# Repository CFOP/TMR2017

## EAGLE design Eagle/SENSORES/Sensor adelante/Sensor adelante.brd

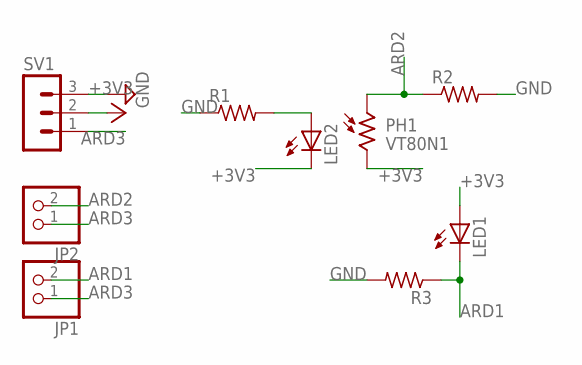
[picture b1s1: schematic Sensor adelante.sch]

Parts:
JP1, JP2: PINHD-1X2; 1X02
LED1, LED2: LED5MM
PH1: VT80N1; VT800
R1, R2, R3: R-US_0207/15; 0207/15
SV1: MA03-1

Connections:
+3V3: LED1.A, LED2.K (C), PH1.2, SV1.2
ARD1: JP1.2, LED1.K (C), R3.1
ARD2: JP2.2, PH1.1, R2.1
ARD3: JP1.1, JP2.1, SV1.1
GND: R1.1, R2.2, R3.2, SV1.3
unnamed: LED2.A, R1.2

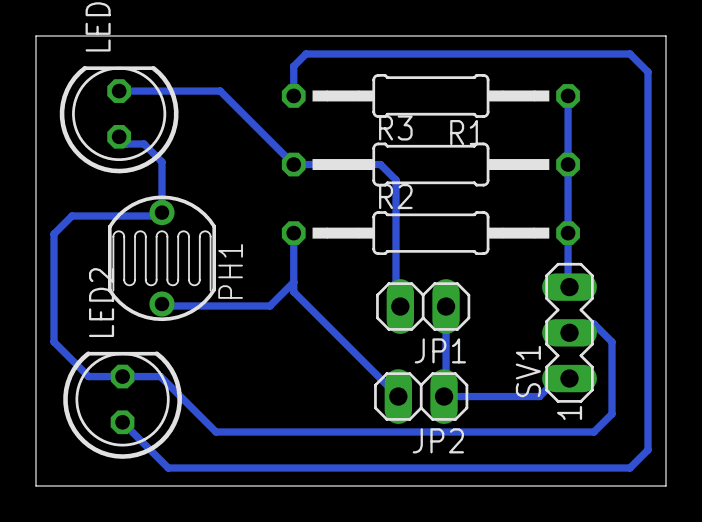
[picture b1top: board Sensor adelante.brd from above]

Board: 2 copper layers, 35.0 x 25.0 mm, 9 parts (0 on the bottom side), 6 nets.

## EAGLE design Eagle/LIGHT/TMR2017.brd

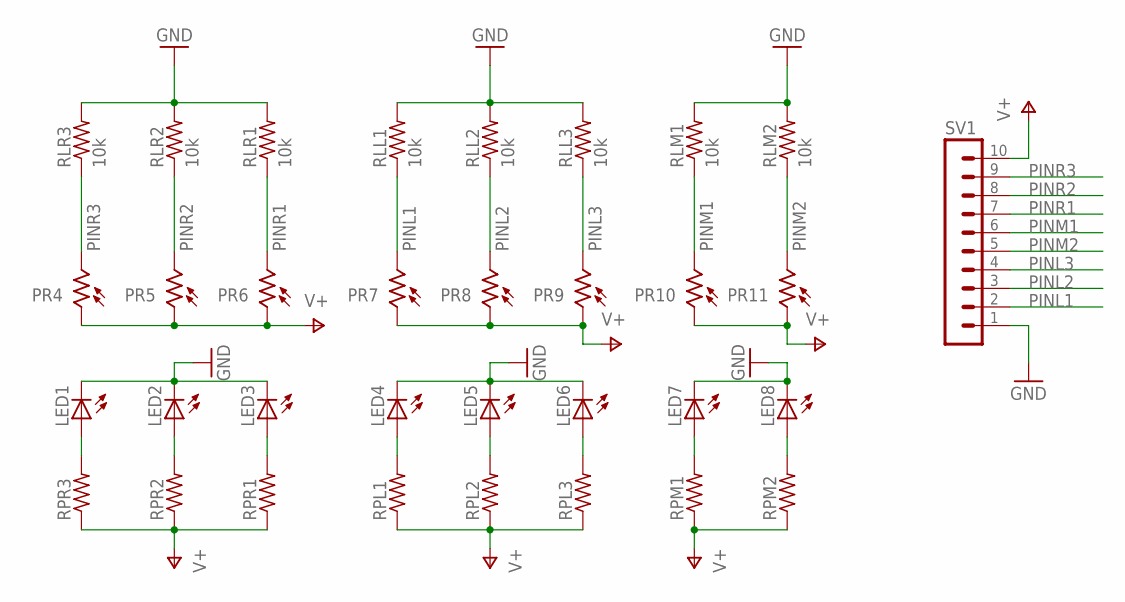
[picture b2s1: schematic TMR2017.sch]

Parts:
LED1, LED2, LED3, LED4, LED5, LED6, LED7, LED8: TLLR4400; LED3MM
PR4, PR5, PR6, PR7, PR8, PR9, PR10, PR11: VT80N1; VT800
RLL1, RLL2, RLL3: 10k; 0207/10
RLM1, RLM2: 10k; 0207/10
RLR1, RLR2, RLR3: 10k; 0207/10
RPL1, RPL2, RPL3: R-US_0207/10; 0207/10
RPM1, RPM2: R-US_0207/10; 0207/10
RPR1, RPR2, RPR3: R-US_0207/10; 0207/10
SV1: MA10-1

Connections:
GND: LED1.K (C), LED2.K (C), LED3.K (C), LED4.K (C), LED5.K (C), LED6.K (C), LED7.K (C), LED8.K (C), RLL1.2, RLL2.2, RLL3.2, RLM1.2, RLM2.2, RLR1.2, RLR2.2, RLR3.2, SV1.1
unnamed: LED1.A, RPR3.2
unnamed: LED2.A, RPR2.2
unnamed: LED3.A, RPR1.2
unnamed: LED4.A, RPL1.2
unnamed: LED5.A, RPL2.2
unnamed: LED6.A, RPL3.2
unnamed: LED7.A, RPM1.2
unnamed: LED8.A, RPM2.2
PINL1: PR7.2, RLL1.1, SV1.2
PINL2: PR8.2, RLL2.1, SV1.3
PINL3: PR9.2, RLL3.1, SV1.4
PINM1: PR10.2, RLM1.1, SV1.6
PINM2: PR11.2, RLM2.1, SV1.5
PINR1: PR6.2, RLR1.1, SV1.7
PINR2: PR5.2, RLR2.1, SV1.8
PINR3: PR4.2, RLR3.1, SV1.9
V+: PR4.1, PR5.1, PR6.1, PR7.1, PR8.1, PR9.1, PR10.1, PR11.1, RPL1.1, RPL2.1, RPL3.1, RPM1.1, RPM2.1, RPR1.1, RPR2.1, RPR3.1, SV1.10

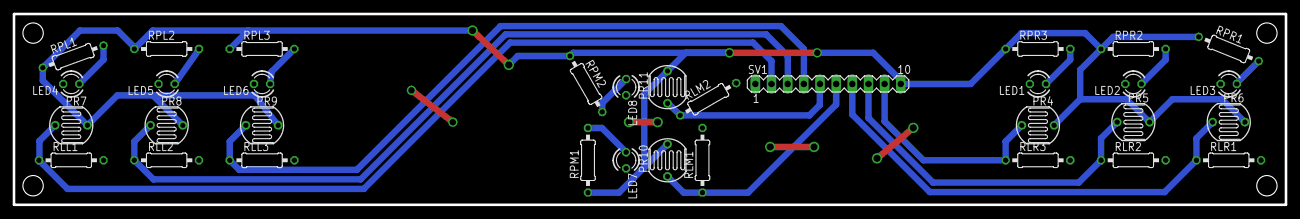
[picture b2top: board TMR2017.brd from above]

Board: 2 copper layers, 200.0 x 30.0 mm, 33 parts (0 on the bottom side), 18 nets.

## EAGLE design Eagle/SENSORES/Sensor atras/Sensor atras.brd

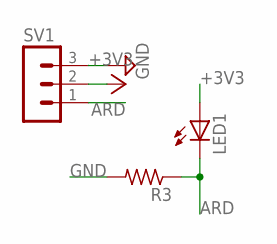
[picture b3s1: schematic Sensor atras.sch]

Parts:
LED1: LED5MM
R3: R-US_0207/15; 0207/15
SV1: MA03-1

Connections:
+3V3: LED1.A, SV1.2
ARD: LED1.K (C), R3.1, SV1.1
GND: R3.2, SV1.3

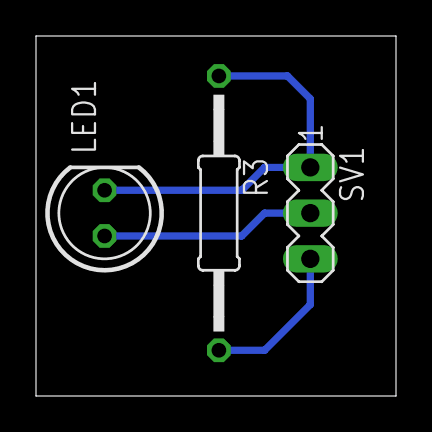
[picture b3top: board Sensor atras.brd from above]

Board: 2 copper layers, 20.0 x 20.0 mm, 3 parts (0 on the bottom side), 3 nets.

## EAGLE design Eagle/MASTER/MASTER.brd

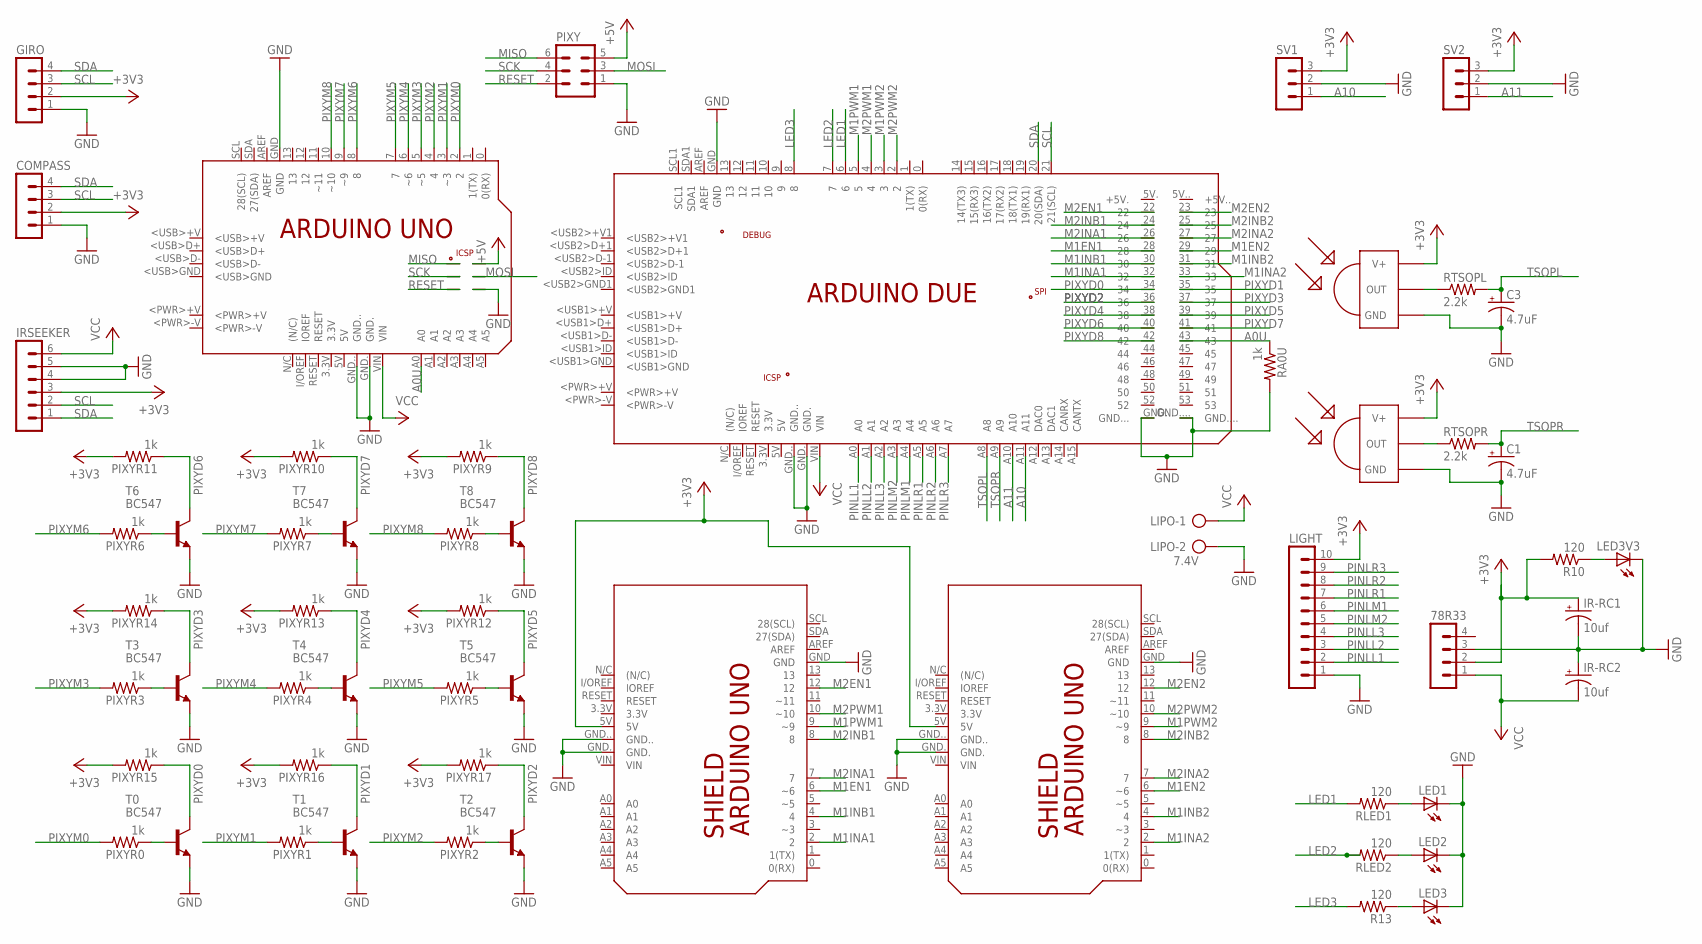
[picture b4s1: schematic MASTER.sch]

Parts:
78R33: MA04-1
C1, C3: 4.7uF; E5-6
COMPASS: MA04-1
GIRO: MA04-1
IR-RC1, IR-RC2: 10uf; E5-6
IRSEEKER: MA06-1
LED1, LED2, LED3, LED3V3: LED5MM
LIGHT: MA10-1
LIPO: 7.4V; AK500/2
PCB3: ARDUINO_DUE
PCB4: ARDUINO_UNO
PIXY: MA03-2
PIXYR0, PIXYR1, PIXYR2, PIXYR3, PIXYR4, PIXYR5, PIXYR6, PIXYR7, PIXYR8, PIXYR9, PIXYR10, PIXYR11, PIXYR12, PIXYR13, PIXYR14, PIXYR15, PIXYR16, PIXYR17: 1k; 0411/15
PUENTE, PUENTE2: SHIELD_UNO
R10, R13: 120; 0411/15
RA0U: 1k; 0411/15
RLED1, RLED2: 120; 0411/15
RTSOPL: 2.2k; 0411/15
RTSOPR: 2.2k; 0411/15
SV1, SV2: MA03-1
T0, T1, T2, T3, T4, T5, T6, T7, T8: BC547; TO92
TSOPL: TSOP2240; TSOP22XX
TSOPR: TSOP2240; TSOP22XX

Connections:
+3V3: 78R33.2, COMPASS.2, GIRO.2, IR-RC1.+, IRSEEKER.3, LIGHT.10, PIXYR9.2, PIXYR10.2, PIXYR11.2, PIXYR12.2, PIXYR13.2, PIXYR14.2, PIXYR15.2, PIXYR16.2, PIXYR17.2, PUENTE.5V, PUENTE2.5V, R10.2, SV1.3, SV2.3, TSOPL.VCC (V+), TSOPR.VCC (V+)
+5V: PCB4.+5V, PIXY.5
A0U: PCB3.43, PCB4.A0, RA0U.1
A10: PCB3.A11, SV1.1
A11: PCB3.A10, SV2.1
GND: 78R33.3, C1.-, C3.-, COMPASS.1, GIRO.1, IR-RC1.-, IR-RC2.+, IRSEEKER.4, IRSEEKER.5, LED1.K (C), LED2.K (C), LED3.K (C), LED3V3.K (C), LIGHT.1, LIPO.2, PCB3.GND, PCB3.GND., PCB3.GND.., PCB3.GND..., PCB3.GND...., PCB4.GND, PCB4.GND., PCB4.GND.., PCB4.GND_, PIXY.1, PUENTE.GND, PUENTE.GND., PUENTE.GND.., PUENTE2.GND, PUENTE2.GND., PUENTE2.GND.., RA0U.2, SV1.2, SV2.2, T0.1 (E), T1.1 (E), T2.1 (E), T3.1 (E), T4.1 (E), T5.1 (E), T6.1 (E), T7.1 (E), T8.1 (E), TSOPL.GND, TSOPR.GND
LED1: PCB3.6, RLED1.2
LED2: PCB3.7, RLED2.2
LED3: PCB3.8, R13.2
M1EN1: PCB3.28, PUENTE.6 (~6)
M1EN2: PCB3.29, PUENTE2.6 (~6)
M1INA1: PCB3.32, PUENTE.2
M1INA2: PCB3.33, PUENTE2.2
M1INB1: PCB3.30, PUENTE.4
M1INB2: PCB3.31, PUENTE2.4
M1PWM1: PCB3.5, PUENTE.9 (~9)
M1PWM2: PCB3.3, PUENTE2.9 (~9)
M2EN1: PCB3.22, PUENTE.12
M2EN2: PCB3.23, PUENTE2.12
M2INA1: PCB3.26, PUENTE.7
M2INA2: PCB3.27, PUENTE2.7
M2INB1: PCB3.24, PUENTE.8
M2INB2: PCB3.25, PUENTE2.8
M2PWM1: PCB3.4, PUENTE.10 (~10)
M2PWM2: PCB3.2, PUENTE2.10 (~10)
MISO: PCB4.MISO, PIXY.6
MOSI: PCB4.MOSI, PIXY.3
unnamed: RTSOPR.1, TSOPR.OUT
unnamed: LED1.A, RLED1.1
unnamed: RTSOPL.1, TSOPL.OUT
unnamed: PIXYR0.1, T0.2 (B)
unnamed: PIXYR1.1, T1.2 (B)
unnamed: PIXYR2.1, T2.2 (B)
unnamed: PIXYR3.1, T3.2 (B)
unnamed: PIXYR4.1, T4.2 (B)
unnamed: PIXYR5.1, T5.2 (B)
unnamed: PIXYR6.1, T6.2 (B)
unnamed: PIXYR7.1, T7.2 (B)
unnamed: PIXYR8.1, T8.2 (B)
unnamed: LED3V3.A, R10.1
PINLL1: LIGHT.2, PCB3.A0
PINLL2: LIGHT.3, PCB3.A1
PINLL3: LIGHT.4, PCB3.A2
PINLM1: LIGHT.6, PCB3.A4
PINLM2: LIGHT.5, PCB3.A3
PINLR1: LIGHT.7, PCB3.A5
PINLR2: LIGHT.8, PCB3.A6
PINLR3: LIGHT.9, PCB3.A7
PIXYD0: PCB3.34, PIXYR15.1, T0.3 (C)
PIXYD1: PCB3.35, PIXYR16.1, T1.3 (C)
PIXYD2: PCB3.36, PIXYR17.1, T2.3 (C)
PIXYD3: PCB3.37, PIXYR14.1, T3.3 (C)
PIXYD4: PCB3.38, PIXYR13.1, T4.3 (C)
PIXYD5: PCB3.39, PIXYR12.1, T5.3 (C)
PIXYD6: PCB3.40, PIXYR11.1, T6.3 (C)
PIXYD7: PCB3.41, PIXYR10.1, T7.3 (C)
PIXYD8: PCB3.42, PIXYR9.1, T8.3 (C)
PIXYM0: PCB4.2, PIXYR0.2
PIXYM1: PCB4.3 (~3), PIXYR1.2
PIXYM2: PCB4.4, PIXYR2.2
PIXYM3: PCB4.5 (~5), PIXYR3.2
PIXYM4: PCB4.6 (~6), PIXYR4.2
PIXYM5: PCB4.7, PIXYR5.2
PIXYM6: PCB4.8, PIXYR6.2
PIXYM7: PCB4.9 (~9), PIXYR7.2
PIXYM8: PCB4.10 (~10), PIXYR8.2
RESET: PCB4.RESET., PIXY.2
RLED2: LED2.A, RLED2.1
RLED3: LED3.A, R13.1
SCK: PCB4.SCK, PIXY.4
SCL: COMPASS.3, GIRO.3, IRSEEKER.2, PCB3.21 (21(SCL))
SDA: COMPASS.4, GIRO.4, IRSEEKER.1, PCB3.20 (20(SDA))
TSOPL: C3.+, PCB3.A8, RTSOPL.2
TSOPR: C1.+, PCB3.A9, RTSOPR.2
VCC: 78R33.1, IR-RC2.-, IRSEEKER.6, LIPO.1, PCB3.VIN, PCB4.VIN

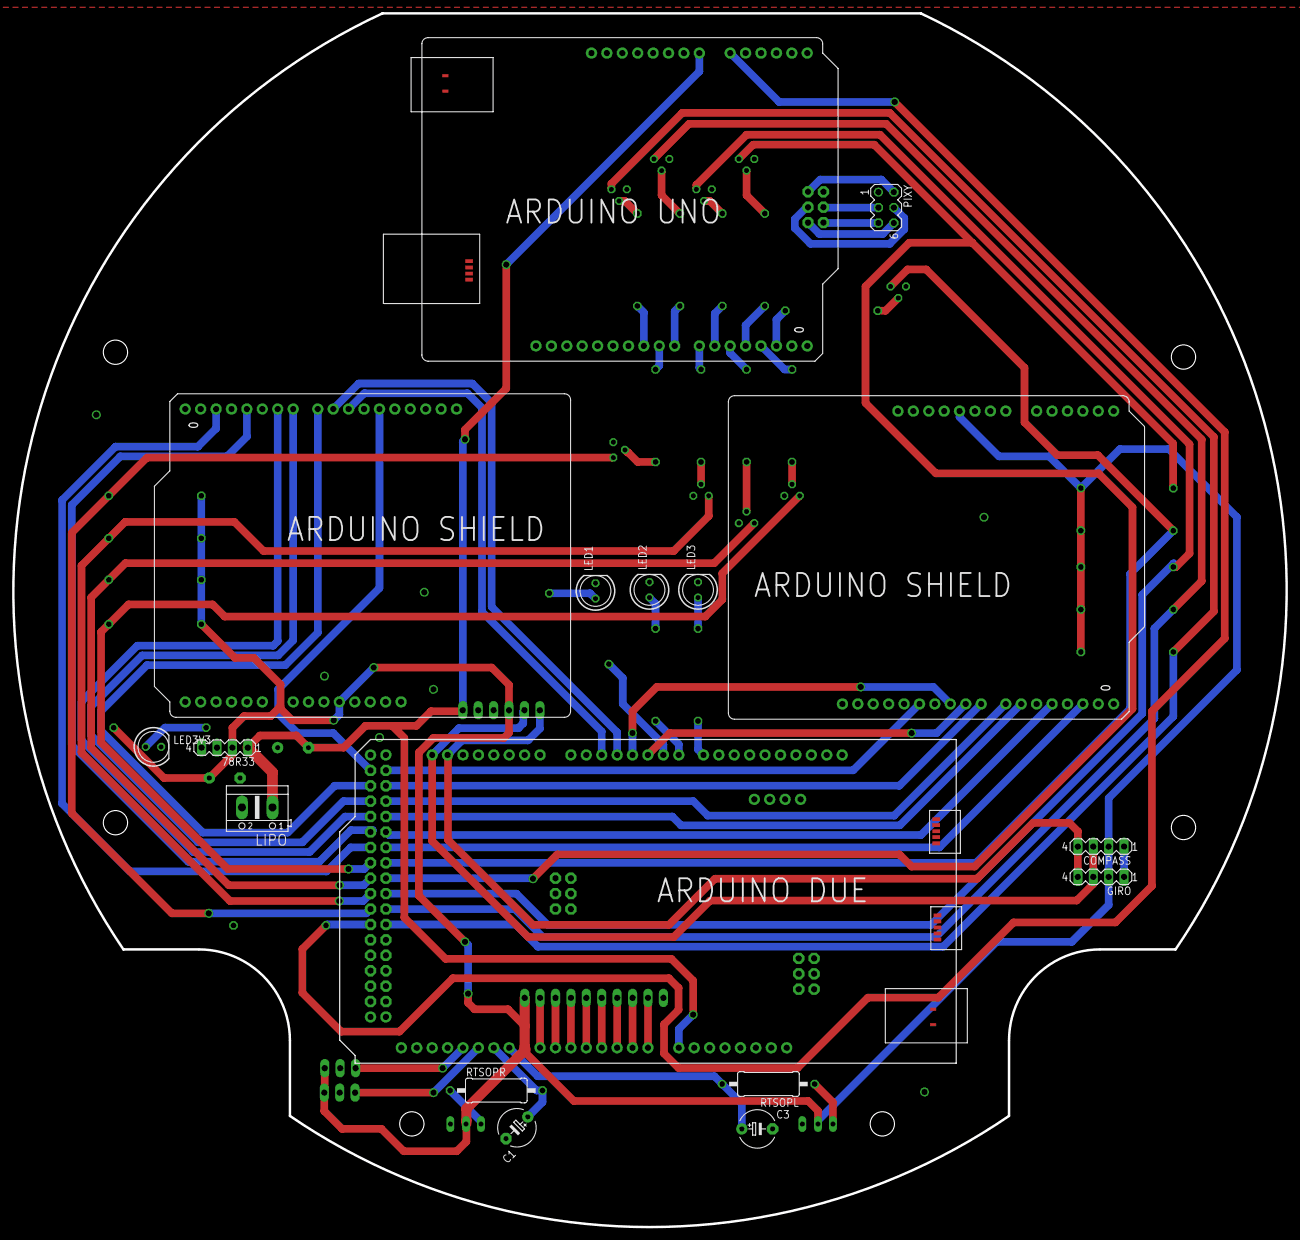
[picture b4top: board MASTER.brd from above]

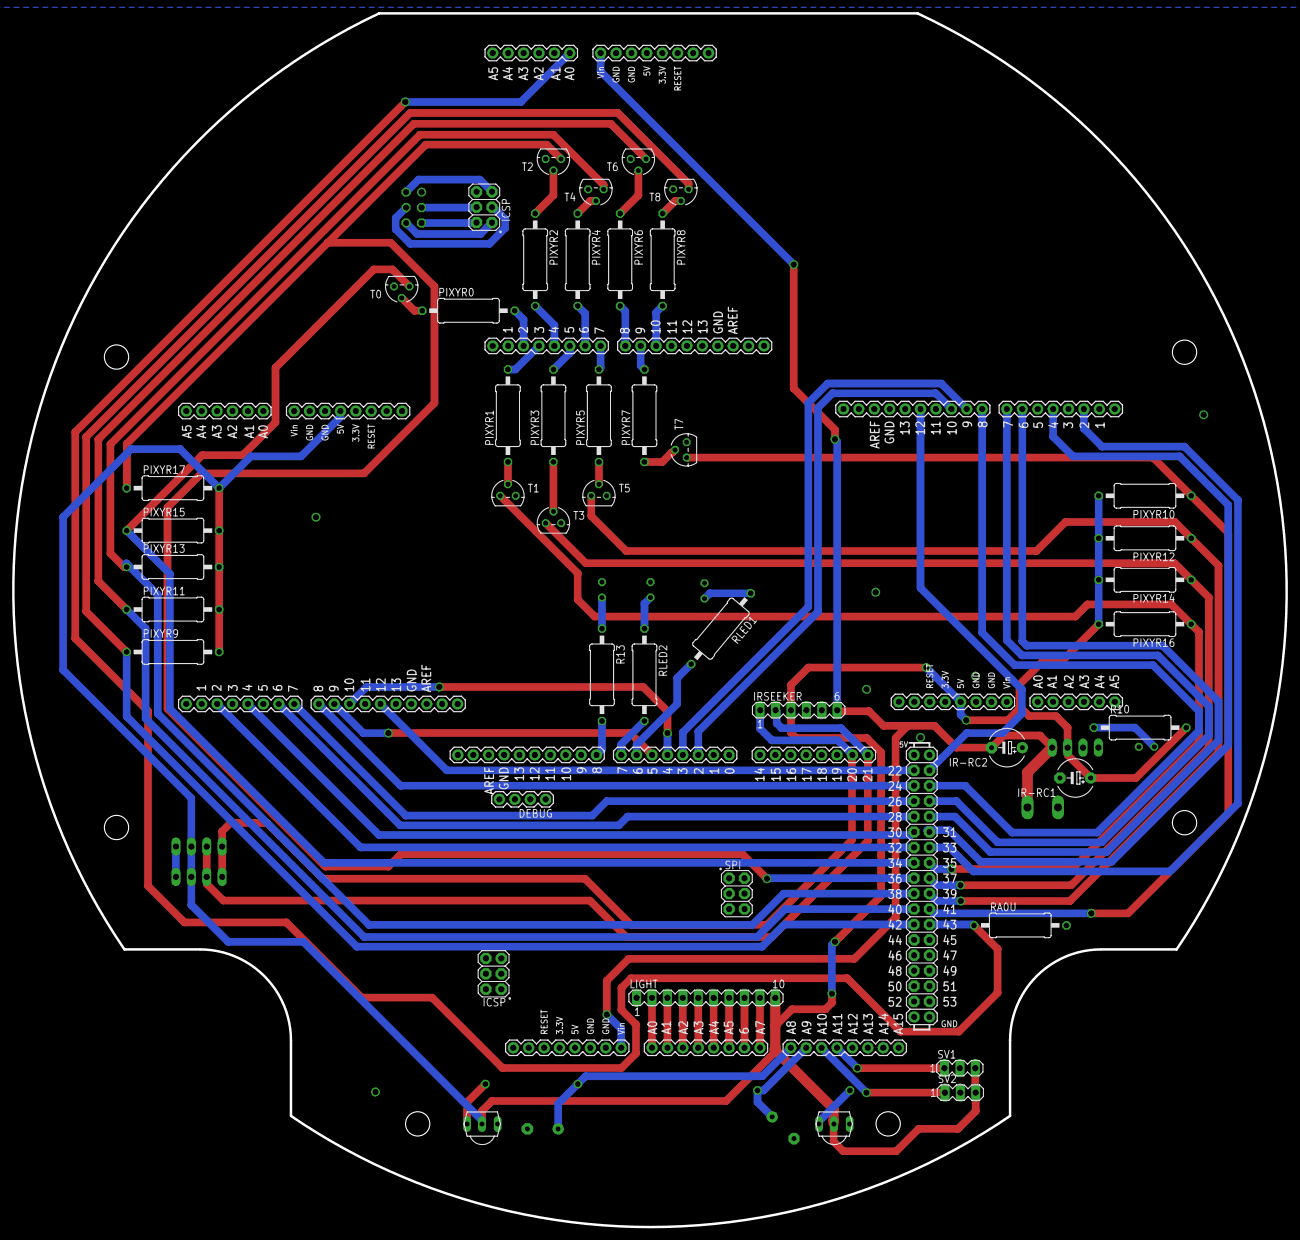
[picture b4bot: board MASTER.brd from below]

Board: 2 copper layers, 209.8 x 200.0 mm, 57 parts (40 on the bottom side), 75 nets.

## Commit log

2017-01-10 Test Lectura
    Prueba de que este leyendo bien
2017-01-12 Test Binary Comunication
    comunicacion de dos arduinos mediante pines digitales
2017-01-26 test binario
    Comunicacion Arduino Uno - Arduino Due mediante bc547 con INPUT_PULLUP
2017-01-26 Pcb eagle
    Diseno de las pcb
2017-02-18 test lightSensor
    prueba de sensor de luz, da r, l, m, o segun en donde vea la linea
    blanca o si no la ve
2017-03-22 Robot Binary Communication Test
2017-03-26 Magnetometer Library
    Fully commented
2017-03-26 Libraries
    Unfinished
2017-06-28 RobotControl v0.1
